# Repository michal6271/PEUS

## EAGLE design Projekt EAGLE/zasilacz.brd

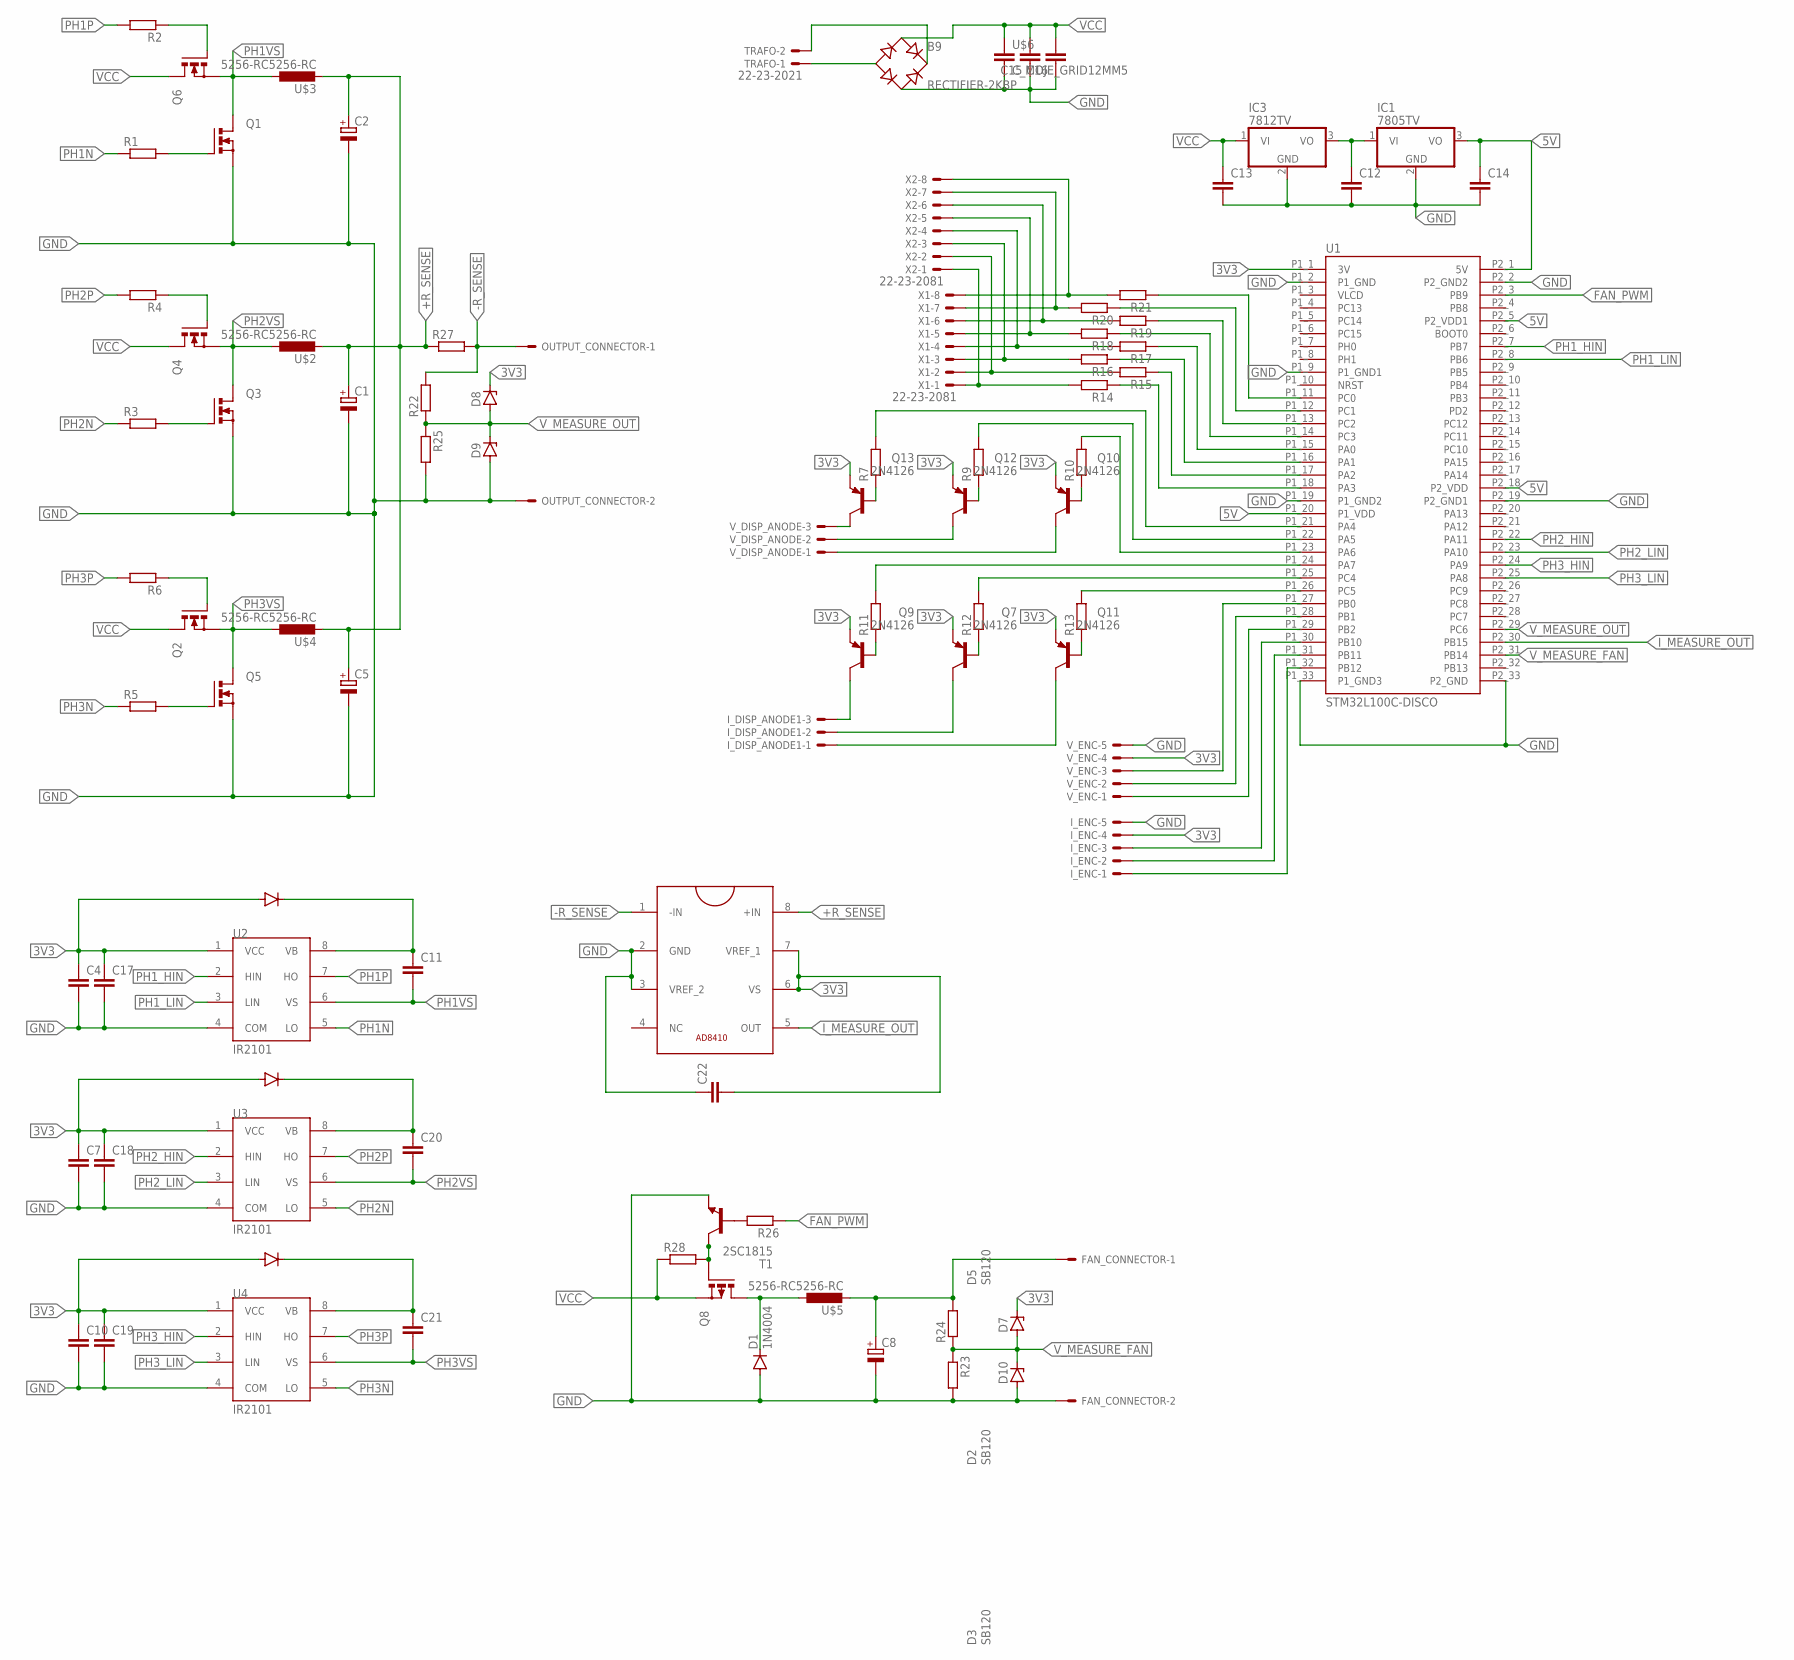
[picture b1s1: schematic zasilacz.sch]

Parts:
B9: RECTIFIER-2KBP; 2KBP
C1, C2, C5, C8: CPOL-EUE5-13; E5-13
C4, C7, C10, C12, C13, C14, C15, C16, C17, C18, C19, C22: C-EU025-024X044; C025-024X044
C11, C20, C21: C-EUC0603K; C0603K
D1: 1N4004; DO41-10
D2, D3, D5: SB120; DO41-10
D7, D8, D9, D10: ZENER-DIODEDO34-7; DO34Z7
FAN_CONNECTOR: 22-23-2021
IC1: 7805TV; TO220V
IC3: 7812TV; TO220V
I_DISP_ANODE1: 22-23-2031
I_ENC: 22-23-2051
OUTPUT_CONNECTOR: 22-23-2021
Q1, Q2, Q3, Q4, Q5, Q6: PMOSFET_NTO220BV; TO220BV
Q7, Q9, Q10, Q11, Q12, Q13: 2N4126; TO92-CBE
Q8: PMOSFET_PTO220BV; TO220BV
R1, R2, R3, R4, R5, R6, R7, R9, R10, R11, R12, R13, R14, R15, R16, R17, R18, R19, R20, R21, R23, R25, R26: R-EU_0309/10; 0309/10
R22, R24: R-EU_0207/12; 0207/12
R27: R-EU_R2512; R2512
R28: R-EU_0207/10; 0207/10
T1: 2SC1815; TO92-ECB
TRAFO: 22-23-2021
U1: STM32L100C-DISCO; DEV_STM32L100C-DISCO
U2, U3, U4: IR2101; DIL08
U$1: AD8410AD8410_V1; AD8410
U$2, U$3, U$4, U$5: 5256-RC5256-RC; INDAD4030W90L3300D1350B
U$6: C_MOJE_GRID12MM5; C025-030X050
V_DISP_ANODE: 22-23-2031
V_ENC: 22-23-2051
X1, X2: 22-23-2081

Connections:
3V3: C4.1, C7.1, C10.1, C17.1, C18.1, C19.1, D2.A, D3.A, D5.A, D7.C, D8.C, I_ENC.4, Q7.E, Q9.E, Q10.E, Q11.E, Q12.E, Q13.E, U1.P1_1 (3V), U2.1 (VCC), U3.1 (VCC), U4.1 (VCC), V_ENC.4
5V: C14.1, IC1.3 (VO), U1.P1_20 (P1_VDD), U1.P2_1 (5V), U1.P2_5 (P2_VDD1), U1.P2_18 (P2_VDD)
+R_SENSE: C1.+, C2.+, C5.+, R27.1, U$1.8 (+IN), U$2.2, U$3.2, U$4.2
-R_SENSE: OUTPUT_CONNECTOR.1, R22.2, R27.2, U$1.1 (-IN)
FAN_PWM: R26.1, U1.P2_3 (PB9)
GND: B9.AC2, C1.-, C2.-, C4.2, C5.-, C7.2, C8.-, C10.2, C12.2, C13.2, C14.2, C15.1, C16.1, C17.2, C18.2, C19.2, C22.1, D1.A, D9.A, D10.A, FAN_CONNECTOR.2, IC1.2 (GND), IC3.2 (GND), I_ENC.5, OUTPUT_CONNECTOR.2, Q1.S, Q3.S, Q5.S, R23.2, R25.2, T1.E, U1.P1_2 (P1_GND), U1.P1_9 (P1_GND1), U1.P1_19 (P1_GND2), U1.P1_33 (P1_GND3), U1.P2_2 (P2_GND2), U1.P2_19 (P2_GND1), U1.P2_33 (P2_GND), U2.4 (COM), U3.4 (COM), U4.4 (COM), U$1.2 (GND), U$1.3 (VREF_2), U$6.2, V_ENC.5
I_MEASURE_OUT: U1.P2_30 (PB15), U$1.5 (OUT)
unnamed: Q8.G, R28.2, T1.C
unnamed: R26.2, T1.B
unnamed: Q3.G, R3.2
unnamed: Q4.G, R4.1
unnamed: R14.1, U1.P1_18 (PA3)
unnamed: R15.1, U1.P1_17 (PA2)
unnamed: Q1.G, R1.2
unnamed: C22.2, U$1.6 (VS), U$1.7 (VREF_1)
unnamed: C12.1, IC1.1 (VI), IC3.3 (VO)
unnamed: Q6.G, R2.1
unnamed: R16.1, U1.P1_16 (PA1)
unnamed: R17.1, U1.P1_15 (PA0)
unnamed: R18.1, U1.P1_14 (PC3)
unnamed: Q5.G, R5.2
unnamed: Q2.G, R6.1
unnamed: R19.1, U1.P1_13 (PC2)
unnamed: Q13.C, V_DISP_ANODE.3
unnamed: R20.1, U1.P1_12 (PC1)
unnamed: B9.+, TRAFO.2
unnamed: Q10.B, R10.1
unnamed: R21.1, U1.P1_11 (PC0)
unnamed: Q12.B, R9.1
unnamed: B9.-, TRAFO.1
unnamed: I_ENC.1, U1.P1_32 (PB12)
unnamed: D1.C, Q8.D, U$5.1
unnamed: Q13.B, R7.1
unnamed: Q12.C, V_DISP_ANODE.2
unnamed: Q10.C, V_DISP_ANODE.1
unnamed: Q11.B, R13.1
unnamed: I_DISP_ANODE1.3, Q9.C
unnamed: I_DISP_ANODE1.2, Q7.C
unnamed: I_DISP_ANODE1.1, Q11.C
unnamed: Q7.B, R12.1
unnamed: Q9.B, R11.1
unnamed: R14.2, X1.1, X2.1
unnamed: R15.2, X1.2, X2.2
unnamed: R16.2, X1.3, X2.3
unnamed: R17.2, X1.4, X2.4
unnamed: R18.2, X1.5, X2.5
unnamed: R19.2, X1.6, X2.6
unnamed: R20.2, X1.7, X2.7
unnamed: R21.2, X1.8, X2.8
unnamed: I_ENC.2, U1.P1_31 (PB11)
unnamed: I_ENC.3, U1.P1_30 (PB10)
unnamed: U1.P1_29 (PB2), V_ENC.1
unnamed: U1.P1_28 (PB1), V_ENC.2
unnamed: U1.P1_27 (PB0), V_ENC.3
unnamed: R13.2, U1.P1_26 (PC5)
unnamed: R12.2, U1.P1_25 (PC4)
unnamed: R11.2, U1.P1_24 (PA7)
unnamed: R10.2, U1.P1_23 (PA6)
unnamed: R9.2, U1.P1_22 (PA5)
unnamed: R7.2, U1.P1_21 (PA4)
PH1N: R1.1, U2.5 (LO)
PH1P: R2.2, U2.7 (HO)
PH1VS: C11.2, Q1.D, Q6.S, U2.6 (VS), U$3.1
PH1_HIN: U1.P2_7 (PB7), U2.2 (HIN)
PH1_LIN: U1.P2_8 (PB6), U2.3 (LIN)
PH2N: R3.1, U3.5 (LO)
PH2P: R4.2, U3.7 (HO)
PH2VS: C20.2, Q3.D, Q4.S, U3.6 (VS), U$2.1
PH2_HIN: U1.P2_22 (PA11), U3.2 (HIN)
PH2_LIN: U1.P2_23 (PA10), U3.3 (LIN)
PH3N: R5.1, U4.5 (LO)
PH3P: R6.2, U4.7 (HO)
PH3VS: C21.2, Q2.S, Q5.D, U4.6 (VS), U$4.1
PH3_HIN: U1.P2_24 (PA9), U4.2 (HIN)
PH3_LIN: U1.P2_25 (PA8), U4.3 (LIN)
UWY: C8.+, FAN_CONNECTOR.1, R24.2, U$5.2
VB: C11.1, C20.1, C21.1, D2.C, D3.C, D5.C, U2.8 (VB), U3.8 (VB), U4.8 (VB)
VCC: B9.AC1, C13.1, C15.2, C16.2, IC3.1 (VI), Q2.D, Q4.D, Q6.D, Q8.S, R28.1, U$6.1
VLCD: U1.P1_3 (VLCD)
V_MEASURE_FAN: D7.A, D10.C, R23.1, R24.1, U1.P2_31 (PB14)
V_MEASURE_OUT: D8.A, D9.C, R22.1, R25.1, U1.P2_29 (PC6)

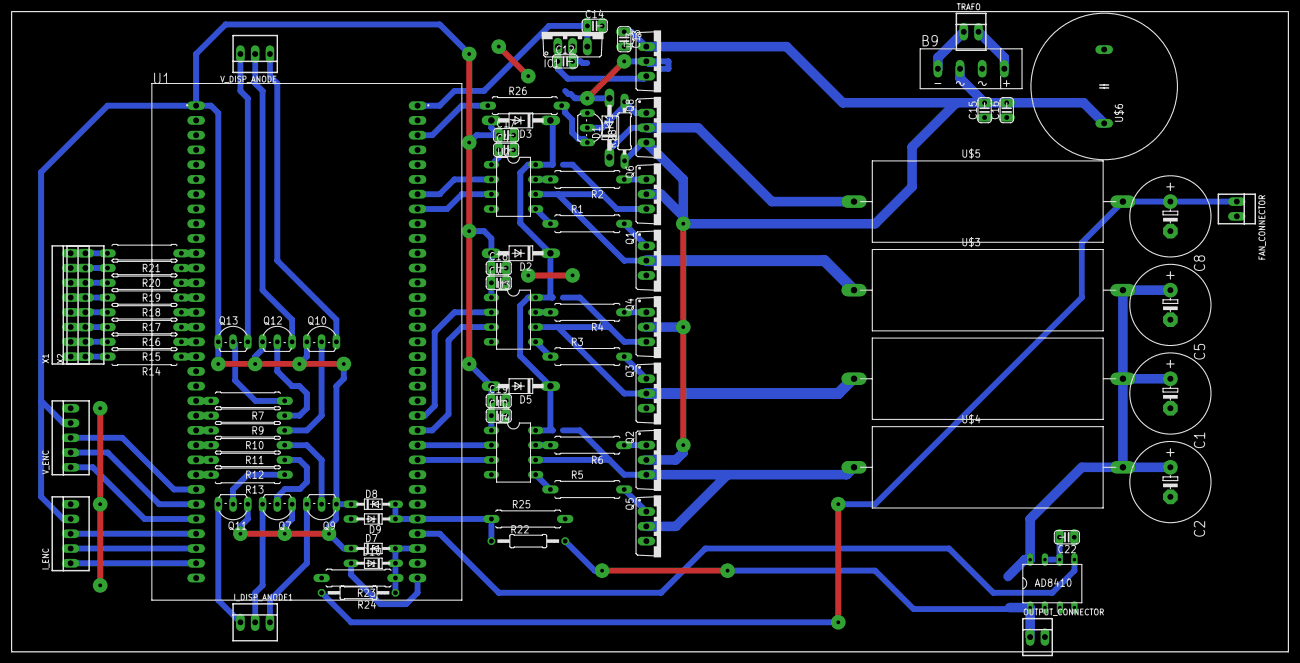
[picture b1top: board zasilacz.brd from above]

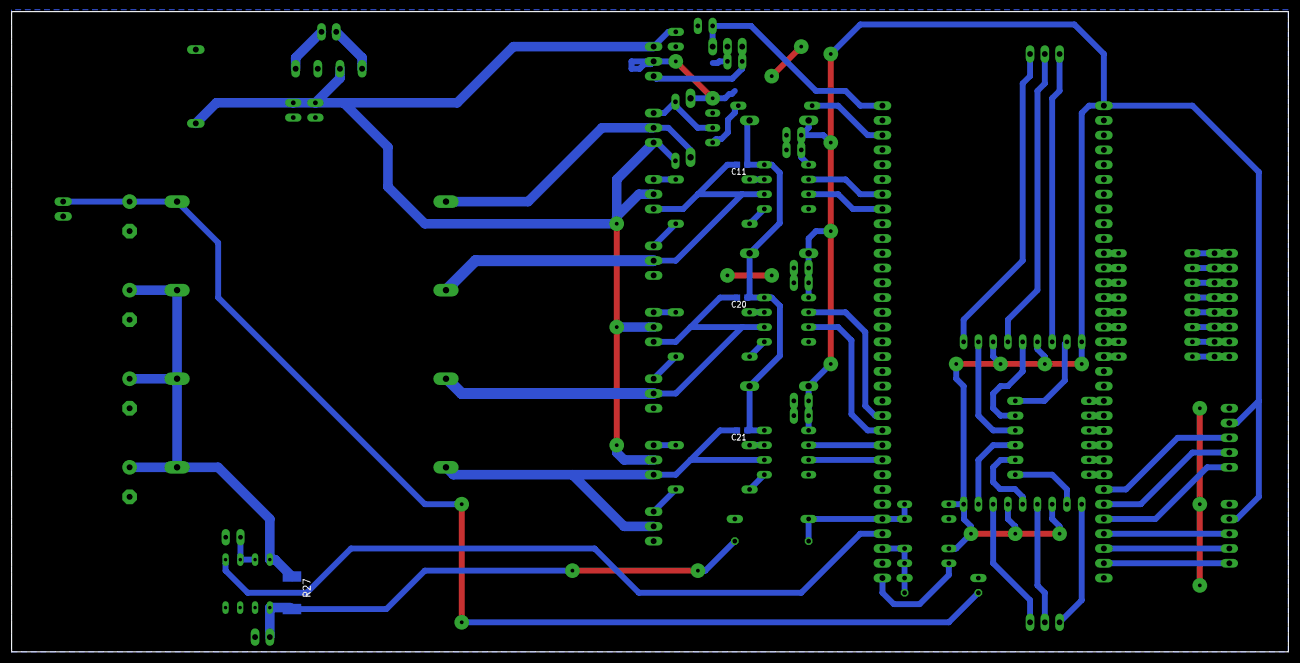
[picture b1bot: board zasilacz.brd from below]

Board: 2 copper layers, 219.7 x 110.2 mm, 90 parts (4 on the bottom side), 80 nets.

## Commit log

2020-10-30 Symulacja w psim
2020-10-30 Zmiana nazwy pliku symulacji
